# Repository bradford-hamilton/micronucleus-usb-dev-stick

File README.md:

First go at building a usb development board using the [ATtiny85](https://www.microchip.com/wwwproducts/en/ATtiny85). I took a [digispark](http://digistump.com/products/1) schematic, modified it to use a [USB Male Type A Connector](https://www.sparkfun.com/products/437), two 1kΩ resistors (where they were blank), placed components on a relatively small footprint, and set up the traces.

The ATtiny85 must be flashed with [micronucleus](https://github.com/micronucleus/micronucleus) (occupies 2kB out of the 8kB flash) to have the ability to be compatible with Arduino's IDE (specifically to be used as a Digispark board). Micronucleus implements [V-USB](https://www.obdev.at/products/vusb/index.html) which is a software-only implementation of a low-speed USB device. Created on [Eagle](https://www.autodesk.com/products/eagle/free-download). Project includes board (.brd), schematic (.sch), a BOM, and all gerber & drill files.

## Status:
- First order came in! Came with some pins pre-soldered, but pins weren't in the order at all :( Need to de-solder to 3D-print a slimmer case as had planned.
- Didn't come with the [USB male type A connectors](https://www.sparkfun.com/products/437)). Will have to order some more separately.
- Waiting on one more shipment of what are basically digispark clones
- ~~Just ordered a handful of the "Board with pins v1" off [PCBWay](https://www.pcbway.com). Will update if they work!~~

___

#### v1 prototype shipped 3/11 front

#### v1 prototype shipped 3/11 back

___

#### Board with pins v1

#### Schematic with pins v1

___

#### Board without pins v1

#### Schematic without pins v1

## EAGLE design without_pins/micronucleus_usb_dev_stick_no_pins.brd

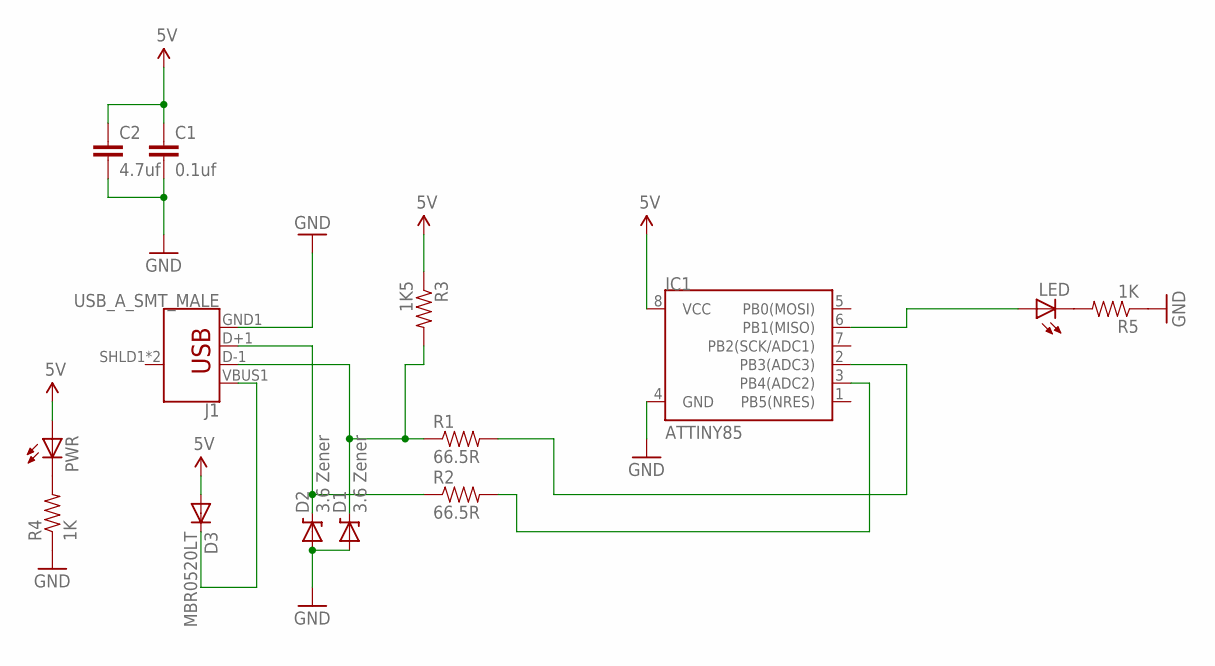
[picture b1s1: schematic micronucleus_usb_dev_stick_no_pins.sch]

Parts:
C1: 0.1uf; 0402-CAP
C2: 4.7uf; 0805
D1, D2: 3.6 Zener; SOD-323
D3: MBR0520LT; SOD123
IC1: ATTINY85; SO08-EIAJ
J1: USB_A_SMT_MALE; USB-A-SMT-MALE
LED: LED0603; LED-0603
PWR: LED0603; LED-0603
R1, R2: 66.5R; 0402-RES
R3: 1K5; 0402-RES
R4, R5: 1K; 0402-RES

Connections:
5V: C1.1, C2.1, D3.A, IC1.8 (VCC), PWR.A, R3.1
GND: C1.2, C2.2, D1.2 (A), D2.2 (A), IC1.4 (GND), J1.GND1 (GND), R4.1, R5.1
unnamed: IC1.2 (PB3(ADC3)), R1.2
unnamed: IC1.6 (PB1(MISO)), LED.A
unnamed: D3.C, J1.VBUS1 (VBUS)
unnamed: IC1.3 (PB4(ADC2)), R2.2
unnamed: D1.1 (C), J1.D-1 (D-), R1.1, R3.2
unnamed: D2.1 (C), J1.D+1 (D+), R2.1
unnamed: LED.C, R5.2
unnamed: PWR.C, R4.2

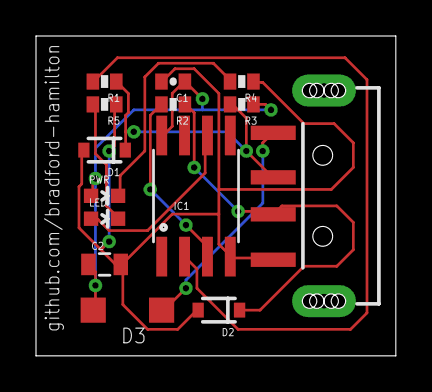
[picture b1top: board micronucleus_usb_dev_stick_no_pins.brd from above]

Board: 2 copper layers, 20.0 x 17.8 mm, 14 parts (0 on the bottom side), 10 nets.

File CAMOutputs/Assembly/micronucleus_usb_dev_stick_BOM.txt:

Partlist exported from /Users/bradford/Downloads/micronucleus_usb_dev_stick copy/micronucleus_usb_dev_stick.sch at 1/14/20 4:32 PM

Qty Value          Device            Package        Parts    Description                                        PROD_ID   
2                  LED0603           LED-0603       LED, PWR LEDs                                                         
1                  M03PTH            1X03           JP2      Header 3                                                     
1                  M06SIP            1X06           JP3      Header 6                                                     
1   0.1uf          CAP0402-CAP       0402-CAP       C1       Capacitor                                                    
2   1K             RESISTOR0402-RES  0402-RES       R4, R5   Resistor                                                     
1   1K5            RESISTOR0402-RES  0402-RES       R3       Resistor                                                     
2   3.6 Zener      DIODE-ZENER-BZT52 SOD-323        D1, D2   Zener Diode                                                  
1   4.7uf          CAP0805           0805           C2       Capacitor                                                    
2   66.5R          RESISTOR0402-RES  0402-RES       R1, R2   Resistor                                                     
1   ATTINY85       ATTINY45          SO08-EIAJ      IC1      Atmel ATTiny45                                               
1   MBR0520LT      MBR0520LT         SOD123         D3       SCHOTTKY BARRIER RECTIFIER                                   
1   MC78M05BDTRKG  LP2950CDT-3.0     DPACK          V1       Source: http://cache.national.com/ds/LP/LP2950.pdf           
1   USB_A_SMT_MALE USB_A_SMT_MALE    USB-A-SMT-MALE J1       USB-A Connector                                    CONN-11499

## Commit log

2020-01-15 Add cam outputs from eagle
2020-01-15 Add board and schematic files
2020-01-15 update bill of materials
2020-01-15 small readme update
2020-01-18 Update repo to contain a micronucleus dev stick with and without pins and all their corresponding files
2020-01-18 readme typo
2020-03-12 add some images and readme updates around first board shipment
2020-03-12 readme update

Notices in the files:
parts and their libraries:
SparkFun: Licensing: CC v3.0 Share-Alike You are welcome to use this library for commercial purposes.
SparkFun-Connectors: Licensing: Creative Commons ShareAlike 4.0 International - https://creativecommons.org/licenses/by-sa/4.0
